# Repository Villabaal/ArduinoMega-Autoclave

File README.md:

# Arduino Mega Autoclave
## Platformio project with avr-gcc 11.2
Autoclave digital controler programmed on platformIO with the arduino framework using c++20 connected via R232 to its interface.

## Kicad project
Folder with kicad files, Schematic, PCB, components list.

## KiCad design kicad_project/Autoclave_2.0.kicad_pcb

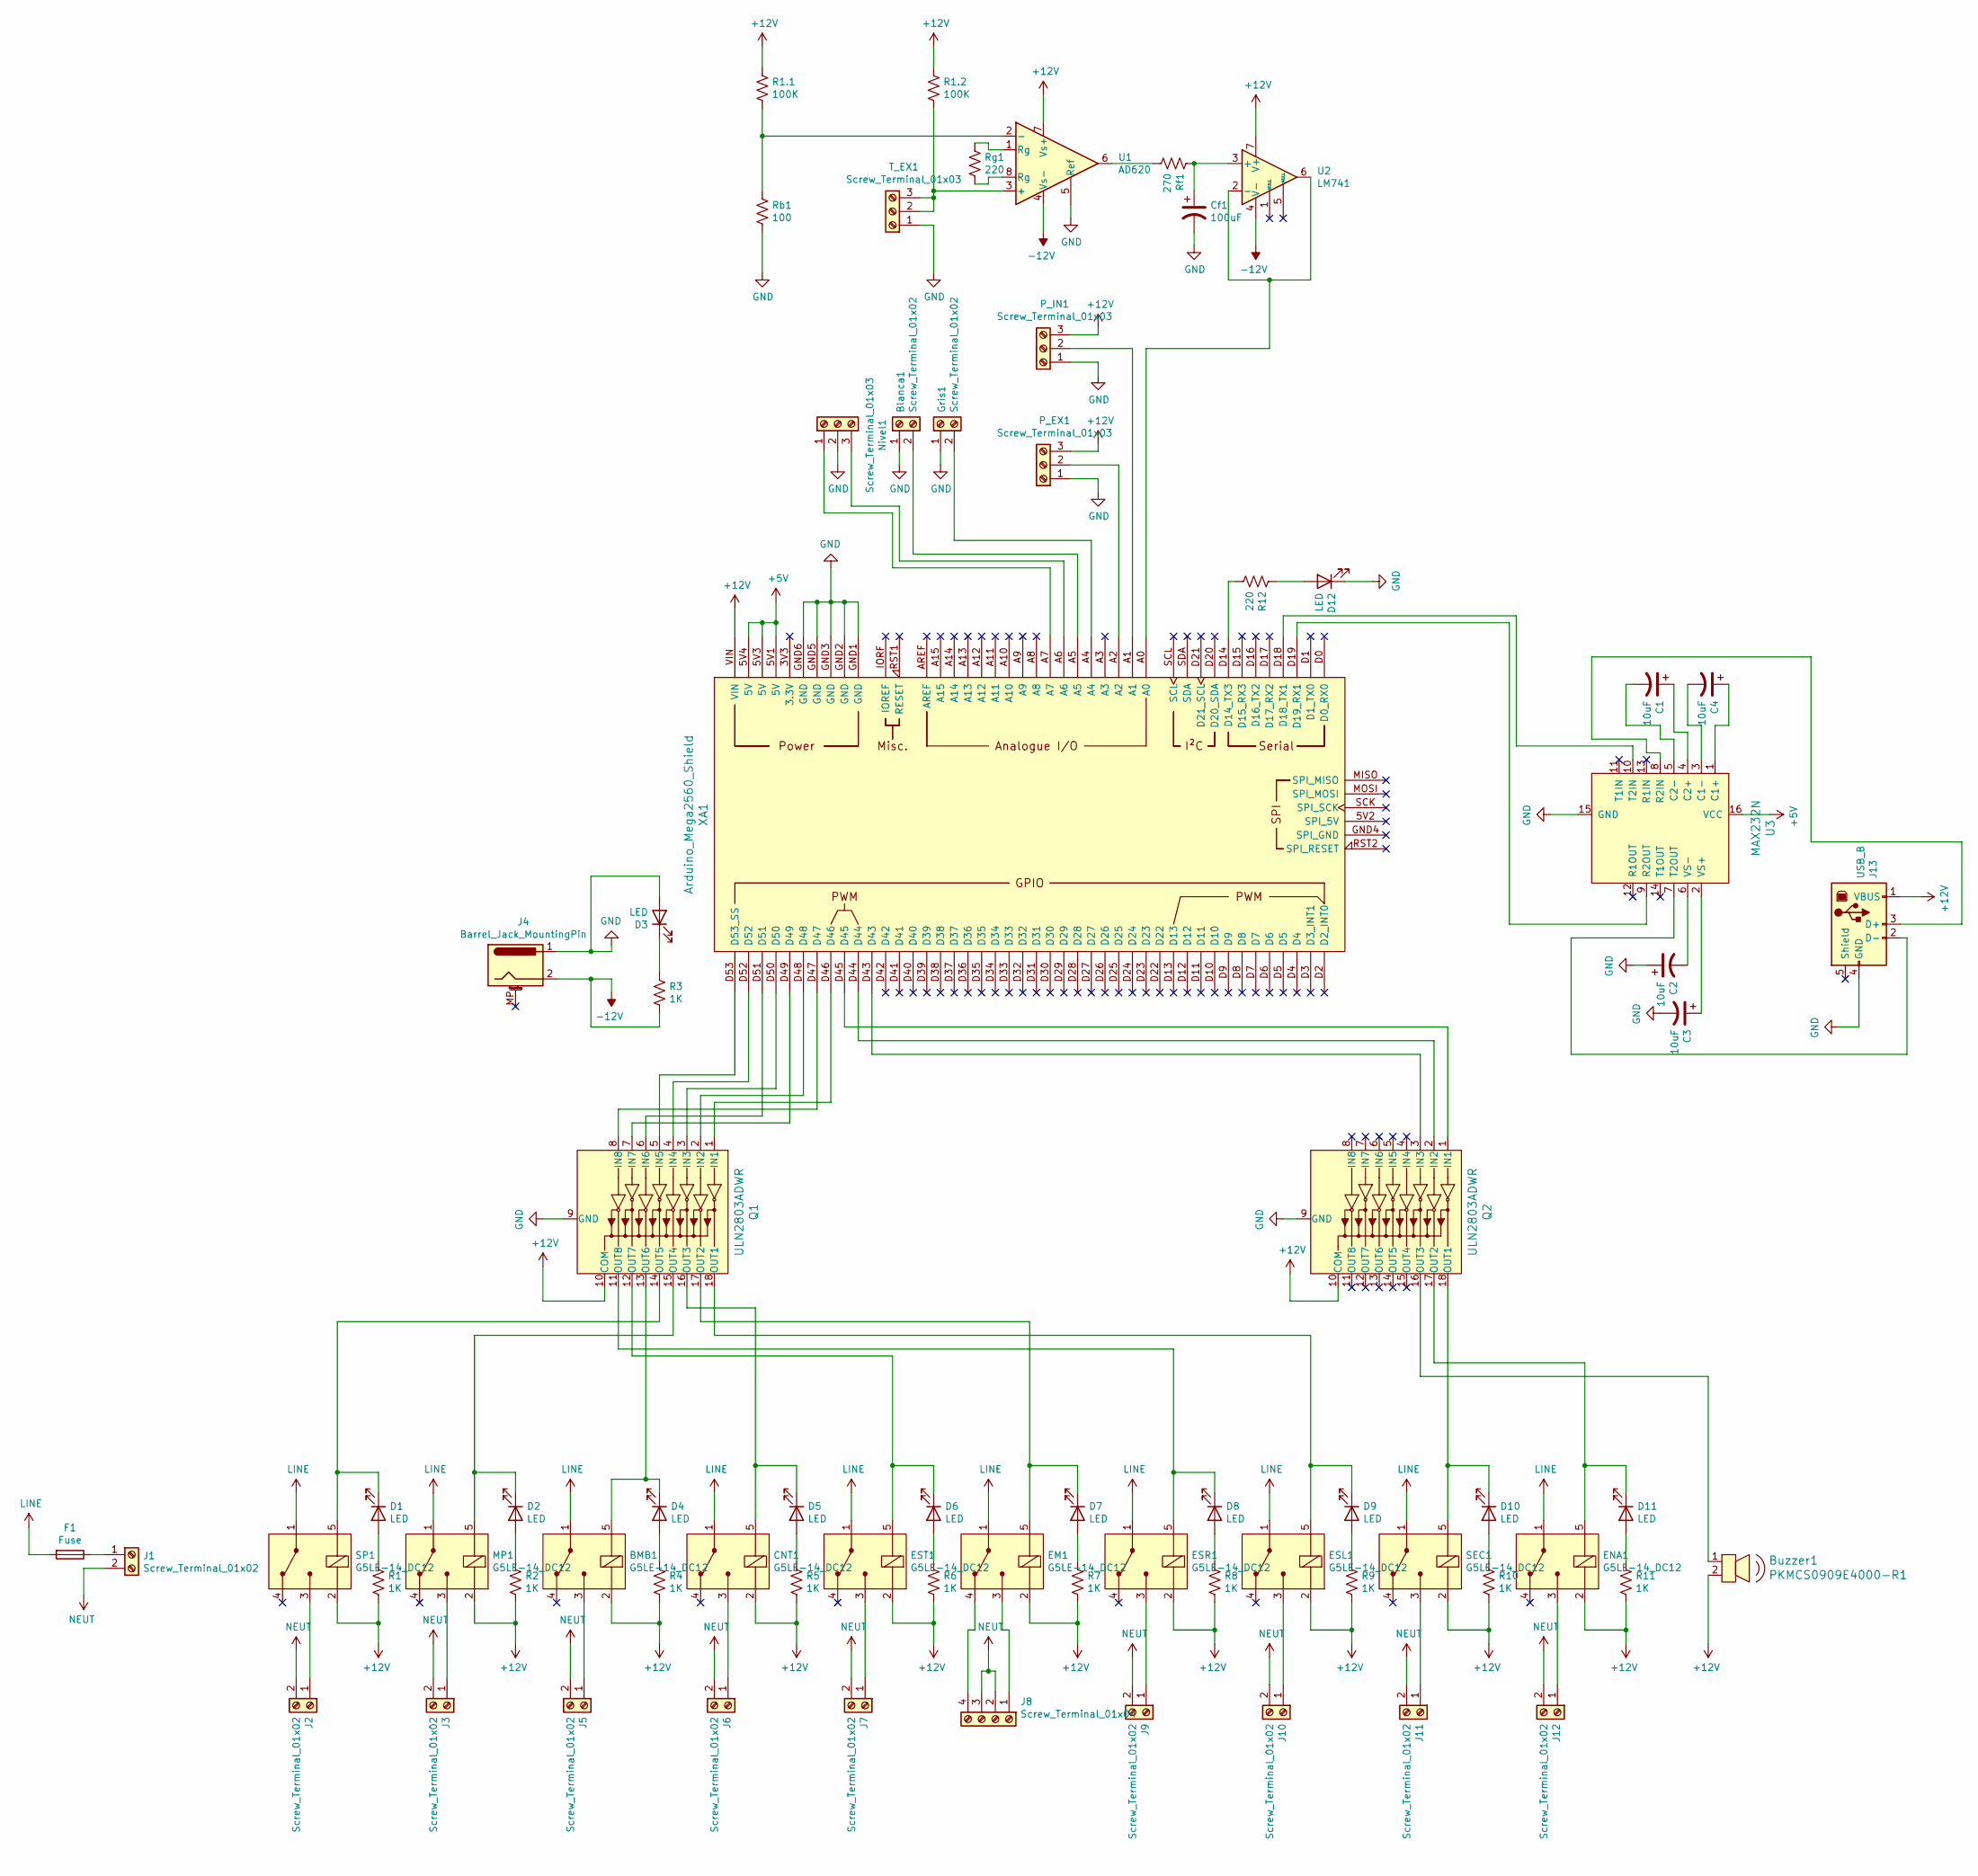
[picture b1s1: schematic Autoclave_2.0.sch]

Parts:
BMB1: G5LE-14_DC12; Relay_SPDT_SANYOU_SRD_Series_Form_C; MPN G5LE-14 DC12; Digi-Key_PN Z1012-ND
Blanca1: Screw_Terminal_01x02; TerminalBlock_MetzConnect_Type055_RT01502HDWU_1x02_P5.00mm_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
Buzzer1: PKMCS0909E4000-R1; Buzzer_12x9.5RM7.6; MPN PKMCS0909E4000-R1; Digi-Key_PN 490-9647-1-ND
C1, C2, C3, C4: 10uF; CP_Radial_D4.0mm_P2.00mm
CNT1: G5LE-14_DC12; Relay_SPDT_SANYOU_SRD_Series_Form_C; MPN G5LE-14 DC12; Digi-Key_PN Z1012-ND
Cf1: 100uF; CP_Radial_D5.0mm_P2.00mm
D1, D2, D3, D4, D5, D6, D7, D8, D9, D10, D11, D12: LED; LED_3mm_Radial
EM1: G5LE-14_DC12; Relay_SPDT_SANYOU_SRD_Series_Form_C; MPN G5LE-14 DC12; Digi-Key_PN Z1012-ND
ENA1: G5LE-14_DC12; Relay_SPDT_SANYOU_SRD_Series_Form_C; MPN G5LE-14 DC12; Digi-Key_PN Z1012-ND
ESL1: G5LE-14_DC12; Relay_SPDT_SANYOU_SRD_Series_Form_C; MPN G5LE-14 DC12; Digi-Key_PN Z1012-ND
ESR1: G5LE-14_DC12; Relay_SPDT_SANYOU_SRD_Series_Form_C; MPN G5LE-14 DC12; Digi-Key_PN Z1012-ND
EST1: G5LE-14_DC12; Relay_SPDT_SANYOU_SRD_Series_Form_C; MPN G5LE-14 DC12; Digi-Key_PN Z1012-ND
F1: Fuse; Fuseholder5x20_horiz_open_inline_Type-I
Gris1: Screw_Terminal_01x02; TerminalBlock_MetzConnect_Type055_RT01502HDWU_1x02_P5.00mm_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
J1, J2, J3, J5, J6, J7, J9, J10, J11, J12: Screw_Terminal_01x02; TerminalBlock_MetzConnect_Type055_RT01502HDWU_1x02_P5.00mm_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
J4: Barrel_Jack_MountingPin; BarrelJack_Horizontal
J8: Screw_Terminal_01x04; TerminalBlock_MetzConnect_Type101_RT01604HBWC_1x04_P5.08mm_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
J13: USB_B; USB_B_OST_USB-B1HSxx_Horizontal
MP1: G5LE-14_DC12; Relay_SPDT_SANYOU_SRD_Series_Form_C; MPN G5LE-14 DC12; Digi-Key_PN Z1012-ND
Nivel1: Screw_Terminal_01x03; TerminalBlock_MetzConnect_Type101_RT01603HBWC_1x03_P5.08mm_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
P_EX1: Screw_Terminal_01x03; TerminalBlock_MetzConnect_Type101_RT01603HBWC_1x03_P5.08mm_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
P_IN1: Screw_Terminal_01x03; TerminalBlock_MetzConnect_Type101_RT01603HBWC_1x03_P5.08mm_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
Q1, Q2: ULN2803ADWR; DIP-18_W7.62mm; MPN ULN2803ADWR; Digi-Key_PN 296-15777-1-ND
R1, R2, R3, R4, R5, R6, R7, R8, R9, R10, R11: 1K; R_Box_L13.0mm_W4.0mm_P9.00mm
R1.1, R1.2: 100K; R_Box_L13.0mm_W4.0mm_P9.00mm
R12: 220; R_Box_L13.0mm_W4.0mm_P9.00mm
Rb1: 100; R_Box_L13.0mm_W4.0mm_P9.00mm
Rf1: 270; R_Box_L13.0mm_W4.0mm_P9.00mm
Rg1: 220; R_Box_L13.0mm_W4.0mm_P9.00mm
SEC1: G5LE-14_DC12; Relay_SPDT_SANYOU_SRD_Series_Form_C; MPN G5LE-14 DC12; Digi-Key_PN Z1012-ND
SP1: G5LE-14_DC12; Relay_SPDT_SANYOU_SRD_Series_Form_C; MPN G5LE-14 DC12; Digi-Key_PN Z1012-ND
T_EX1: Screw_Terminal_01x03; TerminalBlock_MetzConnect_Type101_RT01603HBWC_1x03_P5.08mm_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
U1: AD620; DIP-8_W7.62mm
U2: LM741; DIP-8_W7.62mm
U3: MAX232N; DIP-16_W7.62mm; MPN MAX232N; Digi-Key_PN 296-1402-5-ND
XA1: Arduino_Mega2560_Shield

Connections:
+5V: U3.16 (VCC), XA1.5V1 (5V), XA1.5V3 (5V), XA1.5V4 (5V)
+12V: BMB1.2 (COIL), Buzzer1.2, CNT1.2 (COIL), EM1.2 (COIL), ENA1.2 (COIL), ESL1.2 (COIL), ESR1.2 (COIL), EST1.2 (COIL), J13.1 (VBUS), MP1.2 (COIL), P_EX1.3, P_IN1.3, Q1.10 (COM), Q2.10 (COM), R1.2, R1.1.1, R1.2.1, R2.2, R4.2, R5.2, R6.2, R7.2, R8.2, R9.2, R10.2, R11.2, SEC1.2 (COIL), SP1.2 (COIL), U1.7 (Vs+), U2.7 (V+), XA1.VIN
-12V: J4.2, R3.2, U1.4 (Vs-), U2.4 (V-)
GND: Blanca1.1, C2.1, C3.2, Cf1.2, D3.2 (A), D12.1 (K), Gris1.1, J4.1, J13.4 (GND), Nivel1.2, P_EX1.1, P_IN1.1, Q1.9 (GND), Q2.9 (GND), Rb1.2, T_EX1.1, U1.5 (Ref), U3.15 (GND), XA1.GND1 (GND), XA1.GND2 (GND), XA1.GND3 (GND), XA1.GND5 (GND), XA1.GND6 (GND)
LINE: BMB1.1 (COM), CNT1.1 (COM), EM1.1 (COM), ENA1.1 (COM), ESL1.1 (COM), ESR1.1 (COM), EST1.1 (COM), F1.2, MP1.1 (COM), SEC1.1 (COM), SP1.1 (COM)
NEUT: J1.2, J2.2, J3.2, J5.2, J6.2, J7.2, J8.2, J8.3, J9.2, J10.2, J11.2, J12.2
unnamed: BMB1.3 (NO), J5.1
unnamed: BMB1.5 (COIL), D4.1 (K), Q1.13 (OUT6)
unnamed: Blanca1.2, XA1.A5
unnamed: Buzzer1.1, Q2.16 (OUT3)
unnamed: C1.1, U3.4 (C2+)
unnamed: C1.2, U3.5 (C2-)
unnamed: C2.2, U3.6 (VS-)
unnamed: C3.1, U3.2 (VS+)
unnamed: C4.1, U3.1 (C1+)
unnamed: C4.2, U3.3 (C1-)
unnamed: CNT1.3 (NO), J6.1
unnamed: CNT1.5 (COIL), D5.1 (K), Q1.16 (OUT3)
unnamed: Cf1.1, Rf1.1, U2.3 (+)
unnamed: D1.1 (K), Q1.14 (OUT5), SP1.5 (COIL)
unnamed: D1.2 (A), R1.1
unnamed: D2.1 (K), MP1.5 (COIL), Q1.15 (OUT4)
unnamed: D2.2 (A), R2.1
unnamed: D3.1 (K), R3.1
unnamed: D4.2 (A), R4.1
unnamed: D5.2 (A), R5.1
unnamed: D6.1 (K), EST1.5 (COIL), Q1.12 (OUT7)
unnamed: D6.2 (A), R6.1
unnamed: D7.1 (K), EM1.5 (COIL), Q1.17 (OUT2)
unnamed: D7.2 (A), R7.1
unnamed: D8.1 (K), ESR1.5 (COIL), Q1.11 (OUT8)
unnamed: D8.2 (A), R8.1
unnamed: D9.1 (K), ESL1.5 (COIL), Q1.18 (OUT1)
unnamed: D9.2 (A), R9.1
unnamed: D10.1 (K), Q2.18 (OUT1), SEC1.5 (COIL)
unnamed: D10.2 (A), R10.1
unnamed: D11.1 (K), ENA1.5 (COIL), Q2.17 (OUT2)
unnamed: D11.2 (A), R11.1
unnamed: D12.2 (A), R12.1
unnamed: EM1.3 (NO), J8.1
unnamed: EM1.4 (NC), J8.4
unnamed: ENA1.3 (NO), J12.1
unnamed: ESL1.3 (NO), J10.1
unnamed: ESR1.3 (NO), J9.1
unnamed: EST1.3 (NO), J7.1
unnamed: F1.1, J1.1
unnamed: Gris1.2, XA1.A4
unnamed: J2.1, SP1.3 (NO)
unnamed: J3.1, MP1.3 (NO)
unnamed: J11.1, SEC1.3 (NO)
unnamed: J13.2 (D-), U3.7 (T2OUT)
unnamed: J13.3 (D+), U3.8 (R2IN)
unnamed: Nivel1.1, XA1.A7
unnamed: Nivel1.3, XA1.A6
unnamed: P_EX1.2, XA1.A2
unnamed: P_IN1.2, XA1.A1
unnamed: Q1.1 (IN1), XA1.D46
unnamed: Q1.2 (IN2), XA1.D48
unnamed: Q1.3 (IN3), XA1.D50
unnamed: Q1.4 (IN4), XA1.D52
unnamed: Q1.5 (IN5), XA1.D53 (D53_SS)
unnamed: Q1.6 (IN6), XA1.D51
unnamed: Q1.7 (IN7), XA1.D49
unnamed: Q1.8 (IN8), XA1.D47
unnamed: Q2.1 (IN1), XA1.D45
unnamed: Q2.2 (IN2), XA1.D44
unnamed: Q2.3 (IN3), XA1.D43
unnamed: R1.1.2, Rb1.1, U1.2 (-)
unnamed: R1.2.2, T_EX1.2, T_EX1.3, U1.3 (+)
unnamed: R12.2, XA1.D14 (D14_TX3)
unnamed: Rf1.2, U1.6
unnamed: Rg1.1, U1.1 (Rg)
unnamed: Rg1.2, U1.8 (Rg)
unnamed: U2.2 (-), U2.6, XA1.A0
unnamed: U3.9 (R2OUT), XA1.D19 (D19_RX1)
unnamed: U3.10 (T2IN), XA1.D18 (D18_TX1)

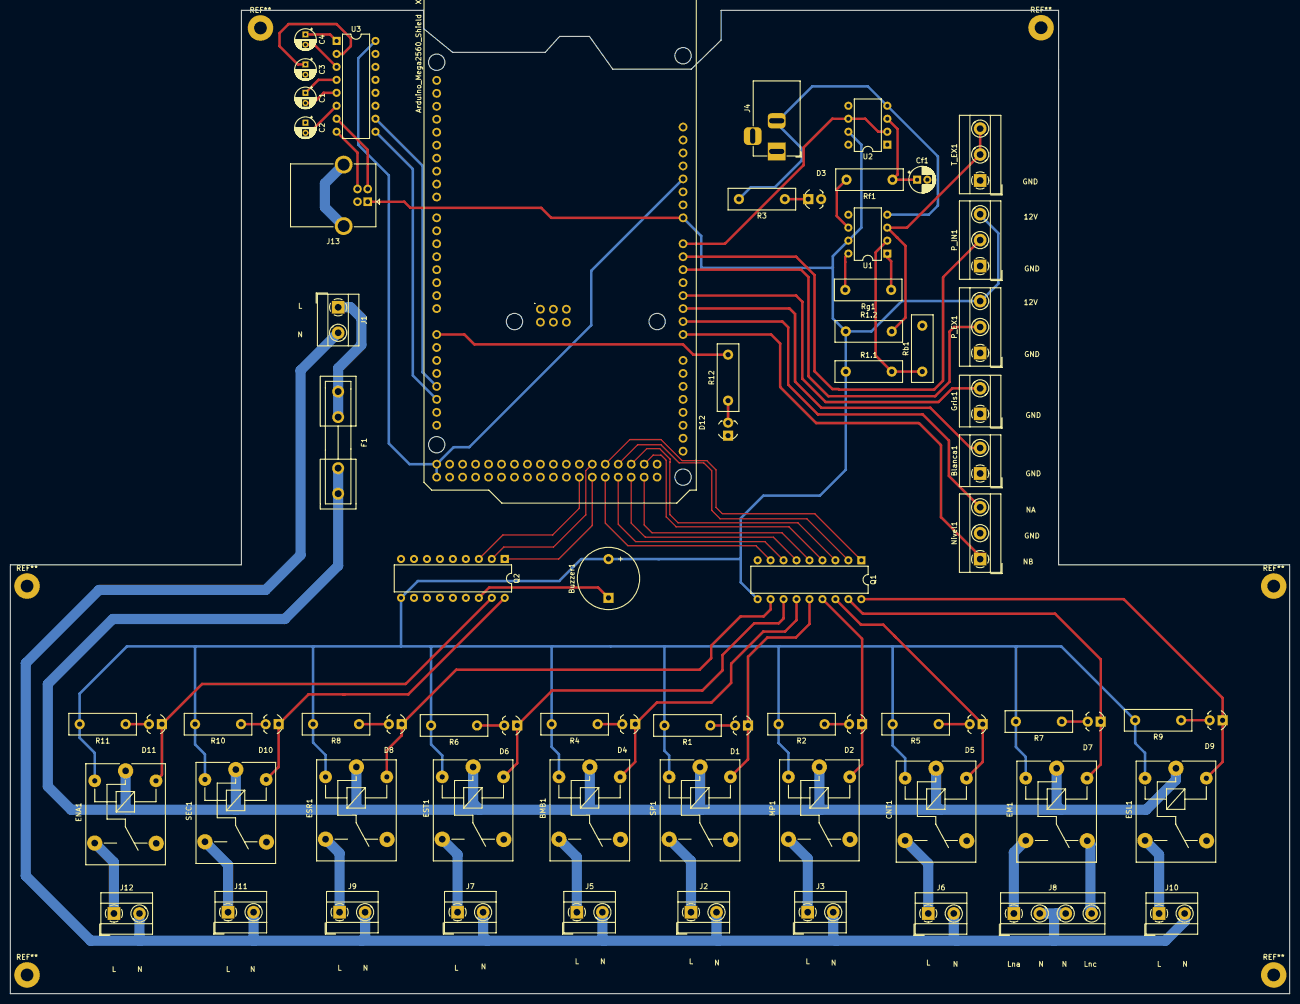
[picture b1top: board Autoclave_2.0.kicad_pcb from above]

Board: 2 copper layers, 250.6 x 192.6 mm, 71 parts (1 on the bottom side), 76 nets.

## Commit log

2023-07-09 template library
2024-03-25 Timers is a Repo
